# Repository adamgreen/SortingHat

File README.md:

# BLE Harry Potter Sorting Hat
This project replaces the original electronics in a [Harry Potter Sorting Hat](https://www.barnesandnoble.com/w/home-gift-harry-potter-sorting-hat/30008992) with a Nordic nRF5 BLE capable device.

## Legal Notes
* This Harry Potter Sorting Hat upgrade is created by a Harry Potter fan for other such fans. It is not sponsored or endorsed by Warner Bros. Entertainment or J.K. Rowling.
* Materials from the Harry Potter series of films are the intellectual property of Warner Bros. Entertainment.

## Project Overview
The user can connect to the device with a BLE capable phone using the Nordic UART service and send **g**, **r**, **h**, or **s** to select the house and then a series of random clips from the movies will play, ending with an announcement of the selected house.

The sound clips are stored on SD card as .wav files and are played back by pulsing a pin as a 1-bit DAC at 22.05kHz. The mouth is connected to a hobby servo instead of the original open-loop DC motor and the position of this servo is based on the volume in upcoming audio buffers.

## Credits
The sound clips and the code flow to randomly select between them originates from the https://github.com/gowenrw/arduino_sorting_hat repository created by [@gowenrw](https://github.com/gowenrw).

This sample is heavily influenced by Nordic's BLE UART Service (ble_app_uart) SDK sample.

## Firmware Build
I have only tested the build on macOS but it might work on other Posix operating systems too.

**Note:** Building the firmware and deploying it to the nRF51 requires the **nrfjprog** tool. The archive for your OS can be downloaded from [here](https://www.nordicsemi.com/Software-and-Tools/Development-Tools/nRF5-Command-Line-Tools). You will also need a SEGGER J-Link JTAG/SWD Debugger. If your projects are of a non-commercial nature, you can use this [low cost module available from Adafruit](https://www.adafruit.com/product/3571).

* `make sdk` will download and install the required Nordic SDK. This should only need to be done once.
* `make audio` will generate the .wav files to be placed in the root folder of the SD card.
* `make flash_softdevice` will install the required Nordic SoftDevice on the nRF51422 microcontroller using the J-Link debugger. This will typically only need to be done once for each microcontroller.
* `make all` will build the hat firmware.
* `make flash` will build the hat firmware and deploy it using the J-Link debugger.

# Bill of Materials
Description | Quantity | Part Number(s)
------------|----------|---------------
[LM386MMX-1 Low Voltage Audio Amplifier](https://www.digikey.com/products/en?keywords=LM386MMX-1/NOPBCT-ND) | 1 | IC1
[MIC5205 Linear Regulator - 3.3V 150mA SOT23-5](https://www.digikey.com/products/en?keywords=576-1259-1-ND) | 1 | U1
[microSD Socket](https://www.sparkfun.com/products/127) | 1 | JP1
[Dynastream N5150M5CD - nRF51422 Module](https://www.digikey.com/products/en?keywords=N5150M5CD) | 1 | U2
[0.01uF Capacitor - 0805](https://www.adafruit.com/product/441) | 1 | C5
[0.1uF Capacitor - 0805](https://www.adafruit.com/product/441) | 4 | C3, C4, C8, C10
[10uF Capacitor (16V) - Tantalum](https://www.digikey.com/products/en?keywords=478-8235-1-ND) | 4 | C1, C2, C6, C7
[220uF Capacitor (10V) - Tantalum](https://www.digikey.com/products/en?keywords=478-6612-1-ND) | 1 | C9
[10kΩ Resistor - 0805](https://www.adafruit.com/product/441) | 1 | R1
[10Ω Resistor - 0805](https://www.adafruit.com/product/441) | 1 | R6
[1kΩ Resistor - 0805](https://www.adafruit.com/product/441) | 3 | R2, R3, R7
[4.7kΩ Resistor - 0805](https://www.adafruit.com/product/441) | 1 | R4
[10kΩ 11-TurnTrimmer Potentiometer](https://www.digikey.com/products/en?keywords=3223W-1-103ECT-ND) | 1 | R5
[Sliding Switch](https://www.digikey.com/products/en?keywords=EG2481-ND) | 1 | S1

# Schematic

# OSHPark Renderings of PCB

# Postmortem
Things that worked well in the current prototype version of this sorting hat as documented here:
* Getting the house selection via BLE from a custom iOS application.
* Changing out the reciprocating mouth mechanism to instead use a servo with a push-rod mechanism. 
* Reading in the .wav files from uSD card.
* Continuing to support the original button on the hat brim for random house selection.

Things that didn't work as well as I had hoped:
* The LM386 as seen in the above schematic was very sensitive to noise in the 5V supply caused by the servo so I ended up removing it and just using a NPN BJT as described [here](https://makezine.com/projects/make-35/advanced-arduino-sound-synthesis/).
* The audio quality was quite low. There was a hum in the audio. Seems like it might have been from noise on the nRF51 sound output pin when it is in the high state.
* While the LM386 volume level was Ok, once I switched it out for a single NPN transistor, the volume level was quite low.
* The PCB should be modified to better fit inside the hat:
  * It is currently too wide at the bottom, to the right of the uSD card reader and I had to file it down. I should have cut the bottom in like the top and put the SD card reader there pointed inwards (to the left). 
  * The power connector is hard to get to since it is right underneath the speaker.
  * I forgot to label the pins for the BATT header.
  * The antenna of the nRF51 module is a bit tight against the side of the hat. Could have narrowed the PCB width down a bit and pulled module to the left a mm or so.
  * The R5 potentiometer was way too close to back edge and actually got bent up by speaker holder.
  * The C1 capacitor should be moved down a bit as it currently hits up against the bottom of the speaker holder.
  
Things I would change if I ever come back to this project to build a newer prototype version:
* Update the PCB to fix the issues mentioned above.
* Switch to using a nRF52 based microcontroller instead. This chip supports DMA based PWM and I2S.
* Use a I2S based amplified DAC such as the [MAX98357A](https://www.adafruit.com/product/3006) to replace the 1-bit DAC and LM386 in the current project. This would probably allow the BLE connection to be maintained while the house announcement was in progress and greatly improve the sound quality.

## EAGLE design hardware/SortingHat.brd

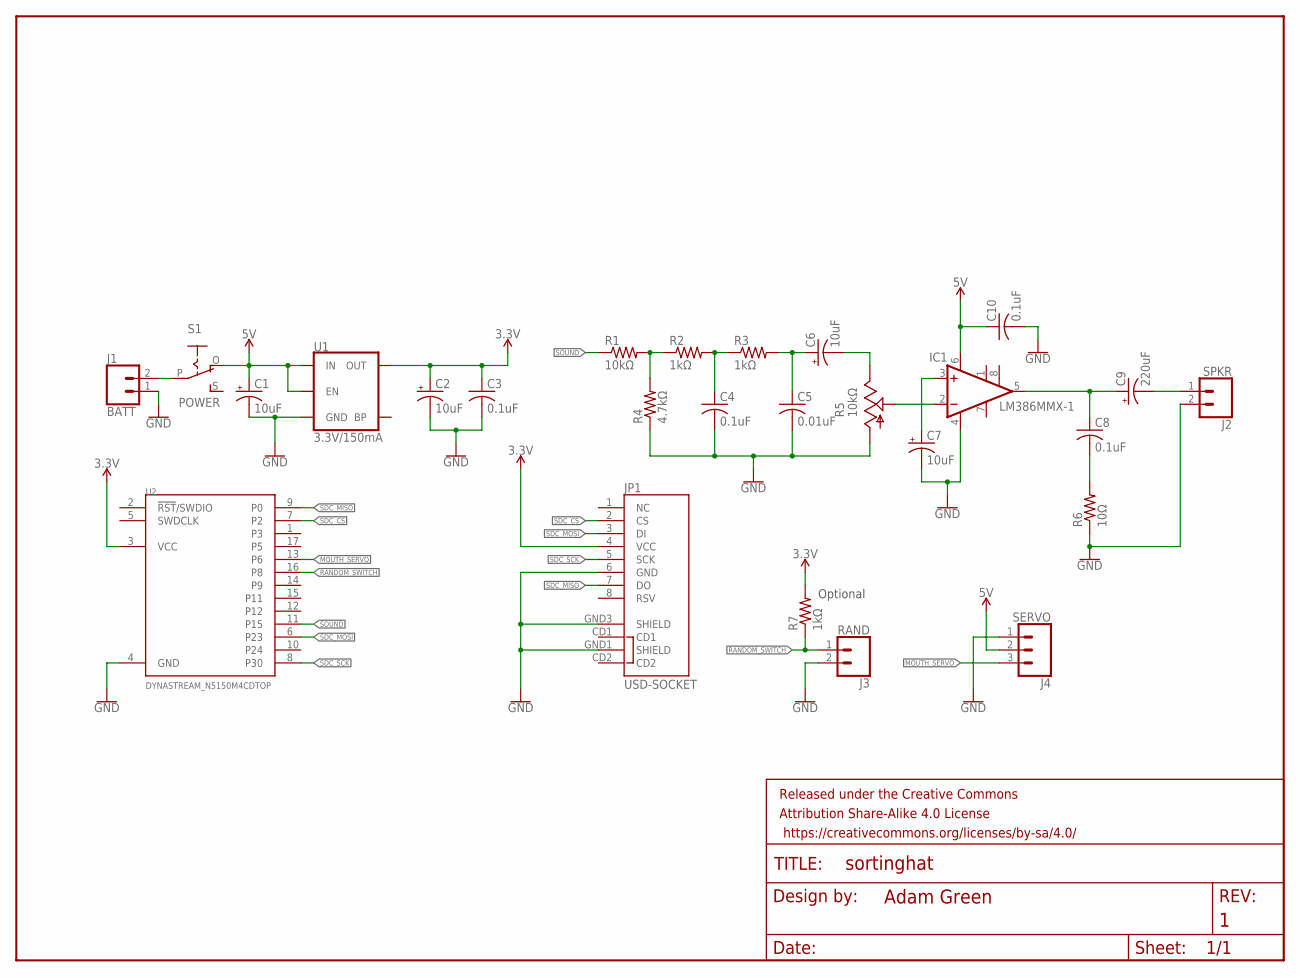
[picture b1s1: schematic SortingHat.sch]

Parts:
C1, C2, C6, C7: 10uF; EIA3216
C3, C4, C8, C10: 0.1uF; C0805
C5: 0.01uF; C0805
C9: 220uF; EIA3528
FRAME1: FRAME-LETTER; CREATIVE_COMMONS
IC1: LM386MMX-1; MMSOP08
J1: BATT; 1X02_NO_SILK
J2: SPKR; 1X02_NO_SILK
J3: RAND; 1X02_NO_SILK
J4: SERVO; 1X03_NO_SILK
JP1: USD-SOCKET; MICROSD_1:1
R1: 10kΩ; R0805
R2, R3, R7: 1kΩ; R0805
R4: 4.7kΩ; R0805
R5: 10kΩ; 3223W
R6: 10Ω; R0805
S1: POWER; EG1218
U1: 3.3V/150mA; SOT23-5
U2: DYNASTREAM_N5150M4CDTOP; N5150M4CD_TOP

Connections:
3.3V: C2.+, C3.1, JP1.4 (VCC), R7.2, U1.5 (OUT), U2.3 (VCC)
5V: C1.+, C10.1, IC1.6 (VS), J4.2, S1.O, U1.1 (IN), U1.3 (EN)
GND: C1.-, C2.-, C3.2, C4.2, C5.2, C7.-, C10.2, IC1.4 (GND), J1.1, J2.2, J3.2, J4.1, JP1.6 (GND), JP1.GND1 (SHIELD), JP1.GND3 (SHIELD), R4.1, R5.1 (A), R6.1, U1.2 (GND), U2.4 (GND)
MOUTH_SERVO: J4.3, U2.13 (P6)
unnamed: J1.2, S1.P
unnamed: R1.2, R2.1, R4.2
unnamed: C4.1, R2.2, R3.1
unnamed: C5.1, C6.+, R3.2
unnamed: C6.-, R5.3 (E)
unnamed: C9.C (-), J2.1
unnamed: IC1.2 (-IN), R5.2 (S)
unnamed: C7.+, IC1.3 (+IN)
unnamed: C8.1, C9.A (+), IC1.5 (OUT)
unnamed: C8.2, R6.2
RANDOM_SWITCH: J3.1, R7.1, U2.16 (P8)
SDC_CS: JP1.2 (CS), U2.7 (P2)
SDC_MISO: JP1.7 (DO), U2.9 (P0)
SDC_MOSI: JP1.3 (DI), U2.6 (P23)
SDC_SCK: JP1.5 (SCK), U2.8 (P30)
SOUND: R1.1, U2.11 (P15)

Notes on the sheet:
Optional

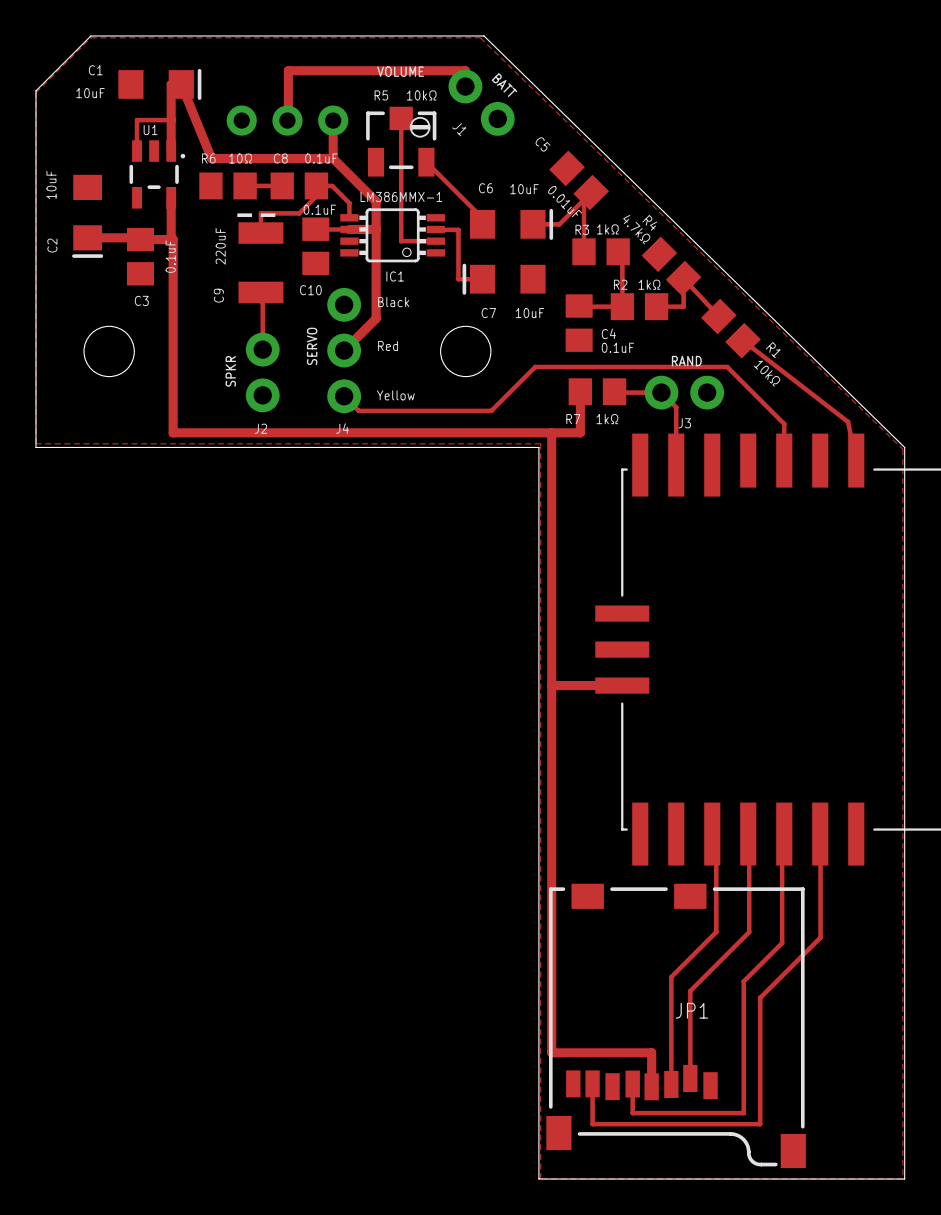
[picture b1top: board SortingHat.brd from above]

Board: 2 copper layers, 48.3 x 63.5 mm, 27 parts (1 on the bottom side), 20 nets.

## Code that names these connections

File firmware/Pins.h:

/*  Copyright (C) 2019  Adam Green (https://github.com/adamgreen)

    This program is free software; you can redistribute it and/or
    modify it under the terms of the GNU General Public License
    as published by the Free Software Foundation; either version 2
    of the License, or (at your option) any later version.

    This program is distributed in the hope that it will be useful,
    but WITHOUT ANY WARRANTY; without even the implied warranty of
    MERCHANTABILITY or FITNESS FOR A PARTICULAR PURPOSE.  See the
    GNU General Public License for more details.
*/
// Defines the pins used for connecting to external hardware.
#ifndef PINS_H_
#define PINS_H_

// Pin to use as output for 1-bit DAC (PWM) sound.
#define SOUND_PIN           15

// Pin to use as output for the mouth servo.
#define MOUTH_SERVO_PIN     6

// Pin to use as input for the random selection switch.
#define RANDOM_SWITCH_PIN   8

// Pins used for interfacing to a SD Card via SPI.
#define SDC_CS_PIN          2
#define SDC_MOSI_PIN        23
#define SDC_MISO_PIN        0
#define SDC_SCK_PIN         30

// Pins used for interfacing to UART with no flow control.
#define UART_RX_PIN         3
#define UART_TX_PIN         5


// Low frequency clock source to be used by the SoftDevice
#define NRF_CLOCK_LFCLKSRC      {.source        = NRF_CLOCK_LF_SRC_XTAL,            \
                                 .rc_ctiv       = 0,                                \
                                 .rc_temp_ctiv  = 0,                                \
                                 .xtal_accuracy = NRF_CLOCK_LF_XTAL_ACCURACY_50_PPM}

#endif // PINS_H_

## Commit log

2019-01-03 Initial commit
    A Bluetooth Low Energy (BLE) enabled Harry Potter Sorting Hat.
    This project replaces the original electronics in the Harry Potter
    Sorting Hat from Barnes and Noble,
    https://www.barnesandnoble.com/w/home-gift-harry-potter-sorting-hat/30008992,
    with a Nordic nRF5 BLE capable device.
    Pins.h contains the definitions for which pins are connected to which
2019-01-03 Generate audio files
    Added the https://github.com/gowenrw/arduino_sorting_hat repository
    from @gowenrw as a submodule. It contains the required audio clips as
    MP3 files. I added an 'audio' rule to my main makefile which is able to
    convert these to the required 22.050kHz mono .wav files required by the
    playback code that I wrote for the nRF51. The generated files should be
    placed in the root folder of the SD card.
2019-01-03 Add GPLv2 license file
2019-01-03 Fix copy/paste error in README
    The build rule portion of the README was copied from my BLE keyboard
    project and referred to "keyboard firmware" when it should have been
    "hat firmware".
2019-01-05 First attempt at schematic
2019-01-07 Version 1 of the PCB
    This is the design as I sent it off to OSHPark.
2019-01-07 Fix typos
    Mostly just fixing typos I noticed in the comments. Also including a
    change to use the ARRAY_SIZE macro instead of hardcoding a size.
2019-01-07 Update license files
    Moved the GPLv2 license from the root of the project into the firmware
    folder and added a CC-BY-SA license file in the hardware folder since
    the 2 parts are covered by different licenses.
2019-01-08 Add version 1 schematic & PCB images
2019-01-08 Update README
    Documenting BOM, schematic, and PCB renderings.
2019-01-16 Update firmware to work on custom board
    Starting bringup on the actual custom PCB. This commit includes:
    * Remove all references to the BSP (board support package) since I have
    no buttons or switches on this custom board. I do still configure
    the random selection switch as I did previously as it was already
    separate from the BSP supported switches.
    * This PCB uses different pins for things like the sound output pin,
2019-01-25 Initial commit of iOS application
    This is a simple application which connects to the Sorting Hat from an
    iPhone for the purpose of selecting the house to be announced. It
    automatically reconnects after the hat finishes its announcement and
    turns the radio back on (once it no longer needs the CPU resources for
    sound playback). The user is presented with 4 buttons, one for each
    house, and will need to press the desired button twice to start the
2019-01-28 Add postmortem to README
    Mostly just notes for what I should change if I ever come back to this project.

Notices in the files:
parts and their libraries:
SparkFun-Capacitors: Licensing: Creative Commons ShareAlike 4.0 International - https://creativecommons.org/licenses/by-sa/4.0
SparkFun-Aesthetics: Released under the Creative Commons Attribution Share-Alike 4.0 License
SparkFun-Aesthetics: https://creativecommons.org/licenses/by-sa/4.0
